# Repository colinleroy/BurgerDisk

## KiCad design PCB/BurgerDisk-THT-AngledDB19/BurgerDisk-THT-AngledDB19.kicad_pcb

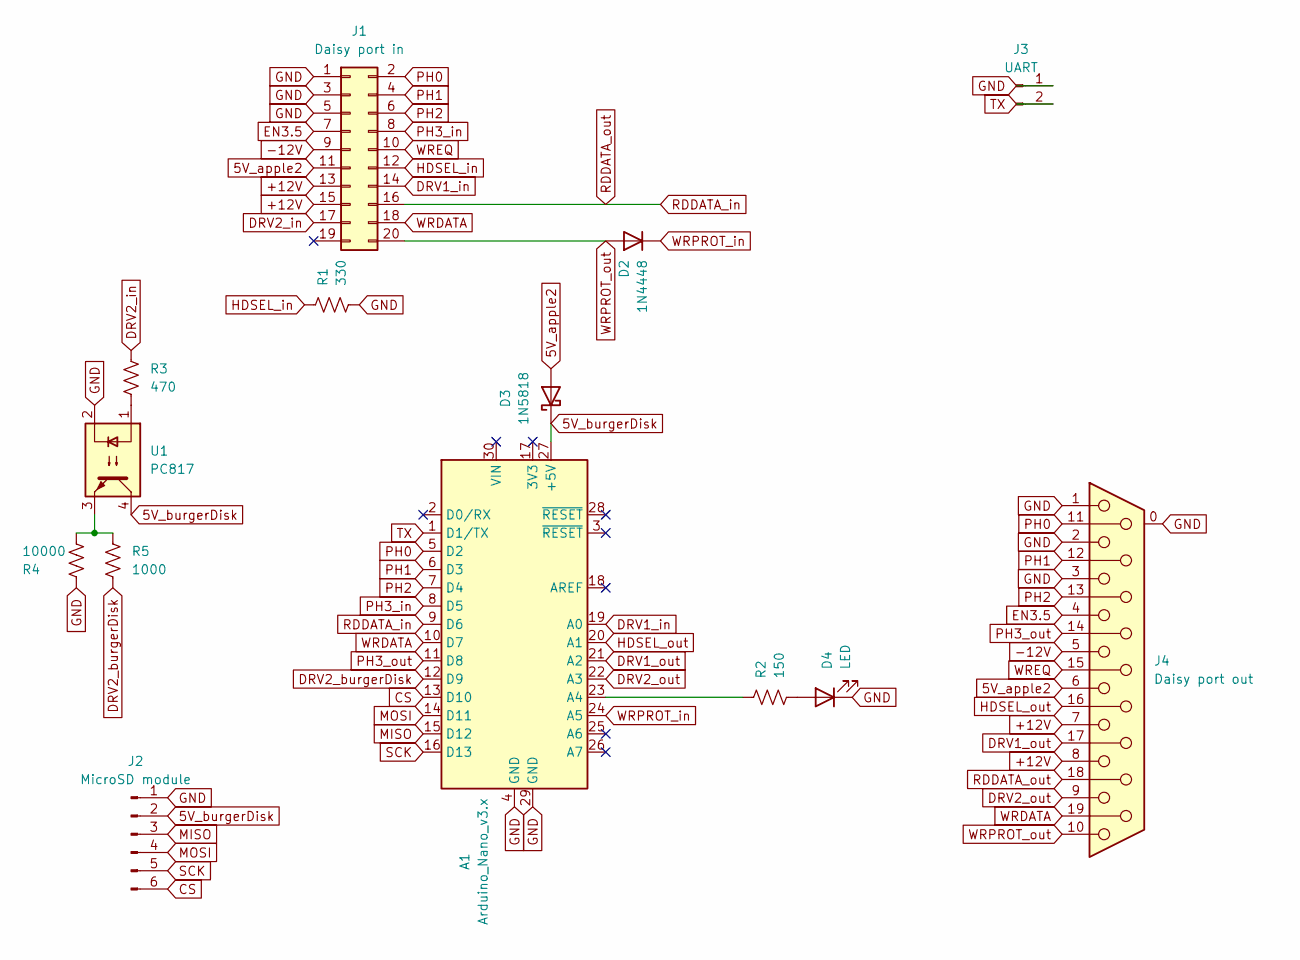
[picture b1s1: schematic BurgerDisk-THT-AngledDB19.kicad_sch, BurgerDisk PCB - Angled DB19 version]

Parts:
A1: Arduino_Nano_v3.x; Arduino_Nano
D2: 1N4448; D_DO-35_SOD27_P7.62mm_Horizontal; LCSC C258170
D3: 1N5818; D_DO-41_SOD81_P7.62mm_Horizontal; LCSC C402217
D4: LED; PinHeader_1x02_P2.54mm_Vertical; LCSC C6273326
J1: Daisy port in; IDC-Header_2x10_P2.54mm_Vertical; LCSC C3405
J2: MicroSD module; PinHeader_1x06_P2.54mm_Vertical; LCSC C56816
J3: UART; PinHeader_1x02_P2.54mm_Vertical; LCSC C6273326
J4: Daisy port out; DSUB-19_Female_Horizontal_MXS82009-8251-9246
R1: 330; R_Axial_DIN0207_L6.3mm_D2.5mm_P7.62mm_Horizontal; LCSC C58608
R2: 150; R_Axial_DIN0207_L6.3mm_D2.5mm_P7.62mm_Horizontal; LCSC C58668
R3: 470; R_Axial_DIN0309_L9.0mm_D3.2mm_P12.70mm_Horizontal; LCSC C129899
R4: 10000; R_Axial_DIN0207_L6.3mm_D2.5mm_P7.62mm_Horizontal; LCSC C57436
R5: 1000; R_Axial_DIN0207_L6.3mm_D2.5mm_P7.62mm_Horizontal; LCSC C57435
U1: PC817; DIP-4_W7.62mm; LCSC C5350

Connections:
5V_apple2: D3.2 (A), J1.11, J4.6
5V_burgerDisk: A1.27 (+5V), D3.1 (K), J2.2, U1.4
+12V: J1.13, J1.15, J4.7, J4.8
-12V: J1.9, J4.5
CS: A1.13 (D10), J2.6
DRV1_in: A1.19 (A0), J1.14
DRV1_out: A1.21 (A2), J4.17
DRV2_burgerDisk: A1.12 (D9), R5.1
DRV2_in: J1.17, R3.1
DRV2_out: A1.22 (A3), J4.9
EN3.5: J1.7, J4.4
GND: A1.4 (GND), A1.29 (GND), D4.1 (K), J1.1, J1.3, J1.5, J2.1, J3.1, J4.0, J4.1, J4.2, J4.3, R1.1, R4.1, U1.2
HDSEL_in: J1.12, R1.2
HDSEL_out: A1.20 (A1), J4.16
MISO: A1.15 (D12), J2.3
MOSI: A1.14 (D11), J2.4
unnamed: A1.23 (A4), R2.2
unnamed: D4.2 (A), R2.1
unnamed: R3.2, U1.1
unnamed: R4.2, R5.2, U1.3
PH0: A1.5 (D2), J1.2, J4.11
PH1: A1.6 (D3), J1.4, J4.12
PH2: A1.7 (D4), J1.6, J4.13
PH3_in: A1.8 (D5), J1.8
PH3_out: A1.11 (D8), J4.14
RDDATA_in: A1.9 (D6), J1.16, J4.18
SCK: A1.16 (D13), J2.5
TX: A1.1 (D1/TX), J3.2
WRDATA: A1.10 (D7), J1.18, J4.19
WREQ: J1.10, J4.15
WRPROT_in: A1.24 (A5), D2.1 (K)
WRPROT_out: D2.2 (A), J1.20, J4.10

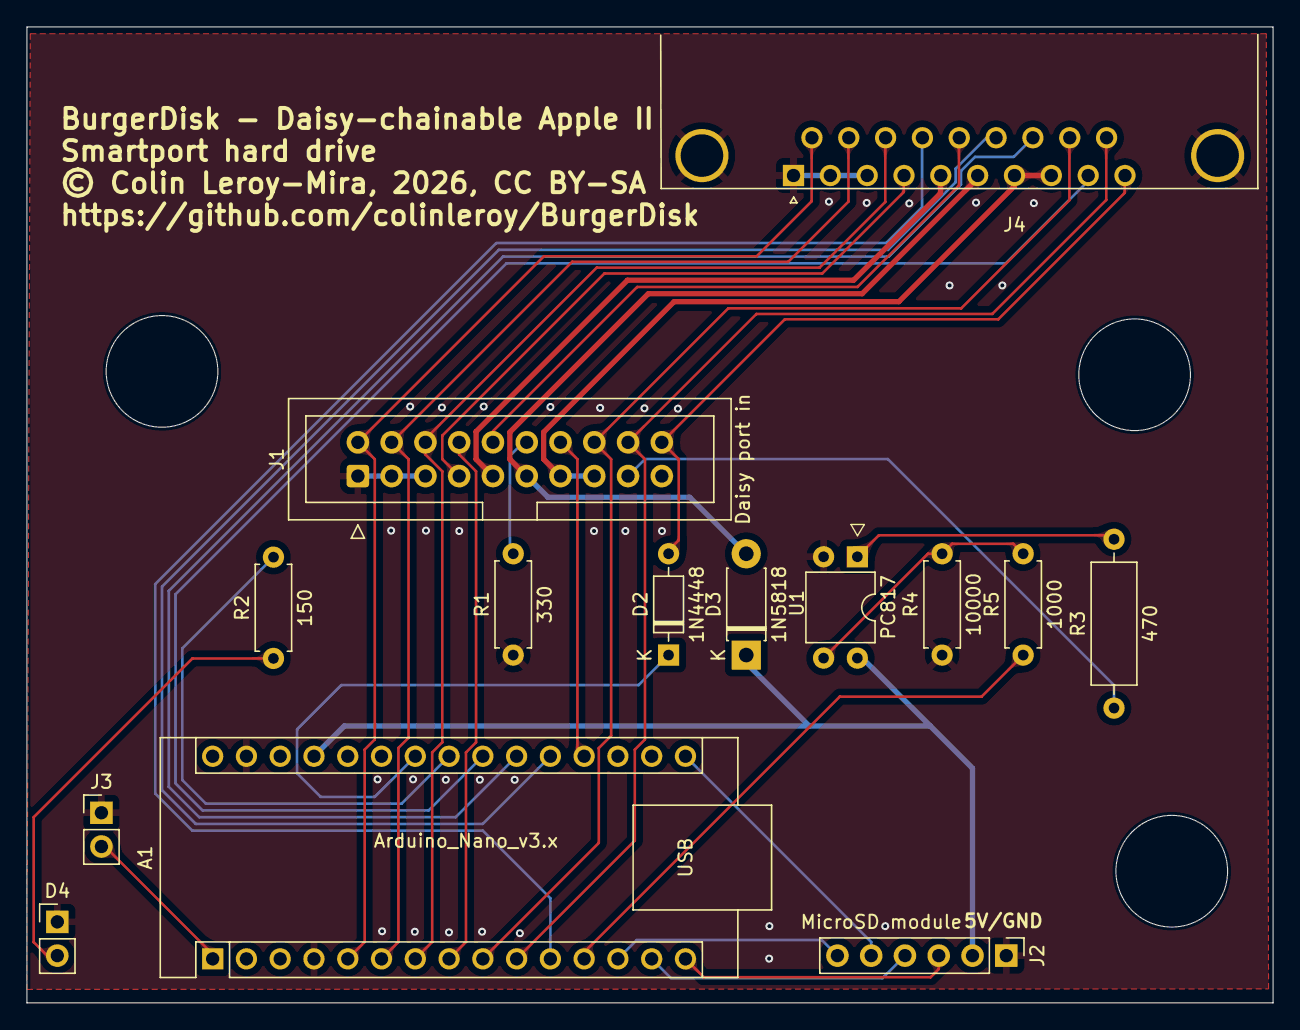
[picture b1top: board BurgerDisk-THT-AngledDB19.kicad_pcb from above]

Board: 2 copper layers, 93.7 x 73.4 mm, 14 parts (0 on the bottom side), 32 nets.

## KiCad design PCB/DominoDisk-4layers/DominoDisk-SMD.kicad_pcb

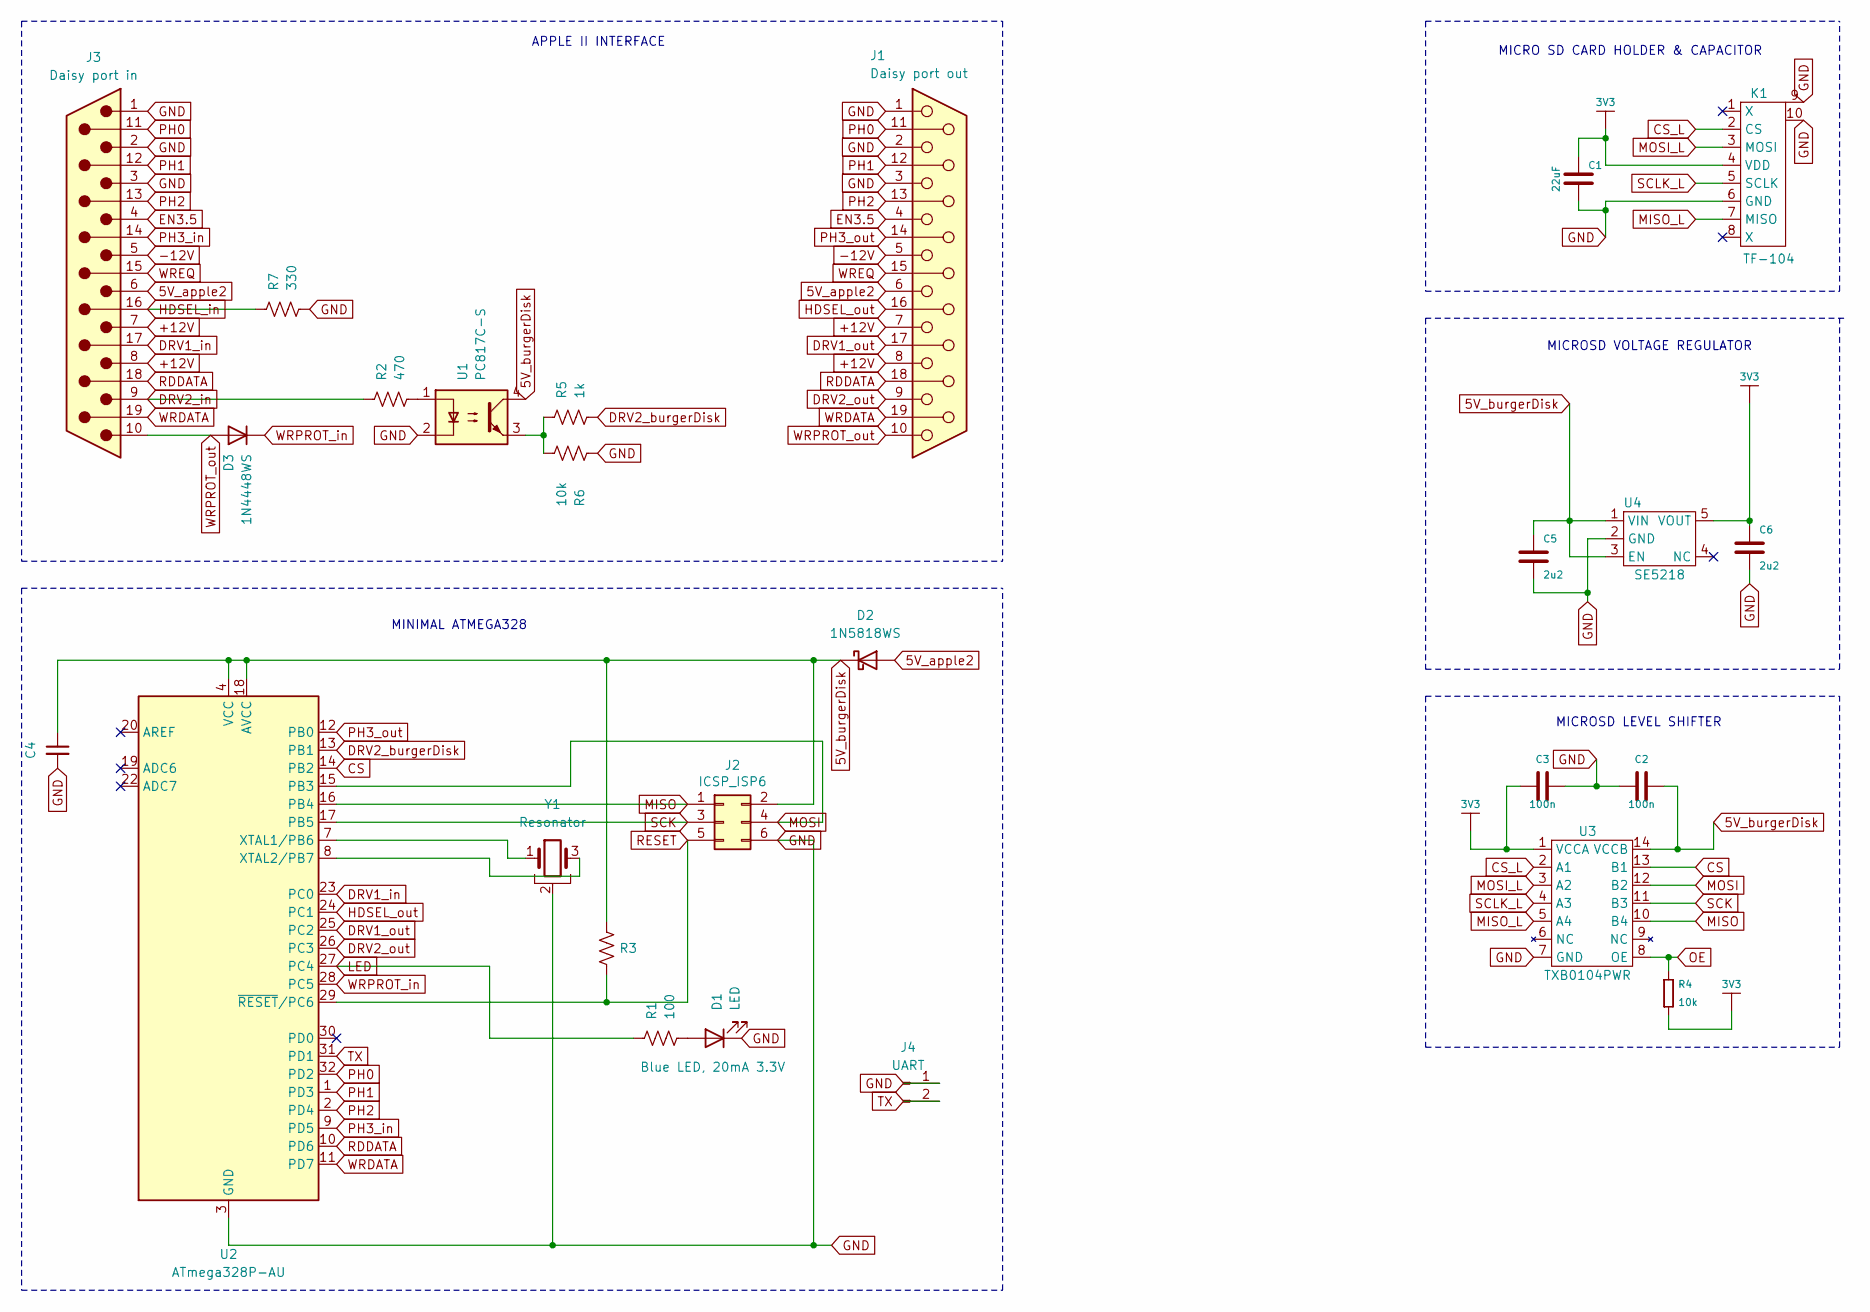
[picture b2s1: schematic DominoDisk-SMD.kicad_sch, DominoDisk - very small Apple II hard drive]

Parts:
C1: 22uF; C_0805_2012Metric; LCSC C45783
C2, C3, C4: 100n; C_0603_1608Metric; LCSC C1590
C5, C6: 2u2; C_0603_1608Metric; LCSC C1607
D1: LED; LED_0603_1608Metric; LCSC C965807
D2: 1N5818WS; D_SOD-123F; LCSC C51315007
D3: 1N4448WS; D_SOD-323F; LCSC C167101
J1: Daisy port out; DSUB-19_Female_EdgeMount_Pitch2.77mm
J2: ICSP_ISP6; PinHeader_2x03_P2.54mm_Horizontal; LCSC C492431
J3: Daisy port in; DSUB-19_Male_EdgeMount_Pitch2.77mm
J4: UART; PinHeader_1x02_P2.54mm_Vertical; LCSC-disabled C6273326 (disabled to avoid having to r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
K1: TF-104; TF-SMD_TF-104; LCSC C266612
R1: 100; R_0603_1608Metric; LCSC C22369795
R2: 470; R_1206_3216Metric; LCSC C137212
R3, R4, R6: 10k; R_0603_1608Metric; LCSC C177337
R5: 1k; R_0603_1608Metric; LCSC C177343
R7: 330; R_0603_1608Metric; LCSC C177341
U1: PC817C-S; SOP-4_3.8x4.1mm_P2.54mm; LCSC C3008369
U2: ATmega328P-AU; TQFP-32_7x7mm_P0.8mm; LCSC C14877
U3: TXB0104PWR; TSSOP-14-1EP_4.4x5mm_P0.65mm; LCSC C60708
U4: SE5218; SOT-23-5; LCSC C118233
Y1: Resonator; Resonator_SMD_Murata_CSTxExxV-3Pin_3.0x1.1mm; LCSC C341521

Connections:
3V3: C1.2, C3.1, C6.2, K1.4 (VDD), R4.1, U3.1 (VCCA), U4.5 (VOUT)
5V_apple2: D2.2 (A), J1.6, J3.6
5V_burgerDisk: C2.2, C4.1, C5.2, D2.1 (K), J2.2, R3.1, U1.4, U2.4 (VCC), U2.6 (VCC), U2.18 (AVCC), U3.14 (VCCB), U4.1 (VIN), U4.3 (EN)
+12V: J1.7, J1.8, J3.7, J3.8
-12V: J1.5, J3.5
CS: U2.14 (PB2), U3.13 (B1)
CS_L: K1.2 (CS), U3.2 (A1)
DRV1_in: J3.17, U2.23 (PC0)
DRV1_out: J1.17, U2.25 (PC2)
DRV2_burgerDisk: R5.1, U2.13 (PB1)
DRV2_in: J3.9, R2.1
DRV2_out: J1.9, U2.26 (PC3)
EN3.5: J1.4, J3.4
GND: C1.1, C2.1, C3.2, C4.2, C5.1, C6.1, D1.1 (K), J1.1, J1.2, J1.3, J2.6, J3.1, J3.2, J3.3, J4.1, K1.6 (GND), K1.9, K1.10, R6.1, R7.1, U1.2, U2.3 (GND), U2.5 (GND), U2.21 (GND), U3.7 (GND), U4.2 (GND), Y1.2
HDSEL_in: J3.16, R7.2
HDSEL_out: J1.16, U2.24 (PC1)
LED: R1.2, U2.27 (PC4)
MISO: J2.1, U2.16 (PB4), U3.10 (B4)
MISO_L: K1.7 (MISO), U3.5 (A4)
MOSI: J2.4, U2.15 (PB3), U3.12 (B2)
MOSI_L: K1.3 (MOSI), U3.3 (A2)
unnamed: D1.2 (A), R1.1
unnamed: R2.2, U1.1
unnamed: R5.2, R6.2, U1.3
unnamed: U2.7 (XTAL1/PB6), Y1.1
unnamed: U2.8 (XTAL2/PB7), Y1.3
OE: R4.2, U3.8 (OE)
PH0: J1.11, J3.11, U2.32 (PD2)
PH1: J1.12, J3.12, U2.1 (PD3)
PH2: J1.13, J3.13, U2.2 (PD4)
PH3_in: J3.14, U2.9 (PD5)
PH3_out: J1.14, U2.12 (PB0)
RDDATA: J1.18, J3.18, U2.10 (PD6)
RESET: J2.5, R3.2, U2.29 (~RESET/PC6)
SCK: J2.3, U2.17 (PB5), U3.11 (B3)
SCLK_L: K1.5 (SCLK), U3.4 (A3)
TX: J4.2, U2.31 (PD1)
WRDATA: J1.19, J3.19, U2.11 (PD7)
WREQ: J1.15, J3.15
WRPROT_in: D3.1 (K), U2.28 (PC5)
WRPROT_out: D3.2 (A), J1.10, J3.10

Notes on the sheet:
MICROSD LEVEL SHIFTER
MINIMAL ATMEGA328
MICROSD VOLTAGE REGULATOR
APPLE II INTERFACE
MICRO SD CARD HOLDER & CAPACITOR

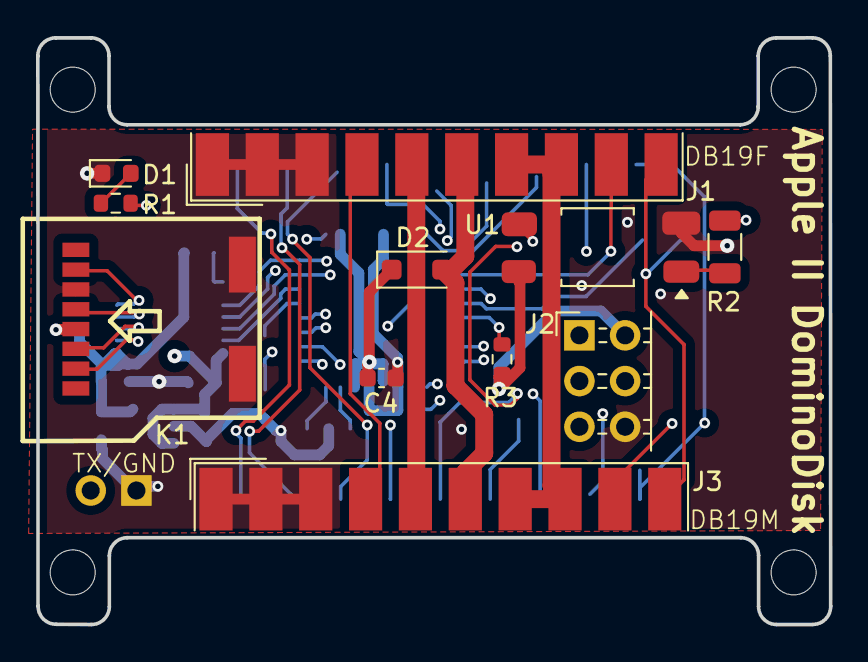
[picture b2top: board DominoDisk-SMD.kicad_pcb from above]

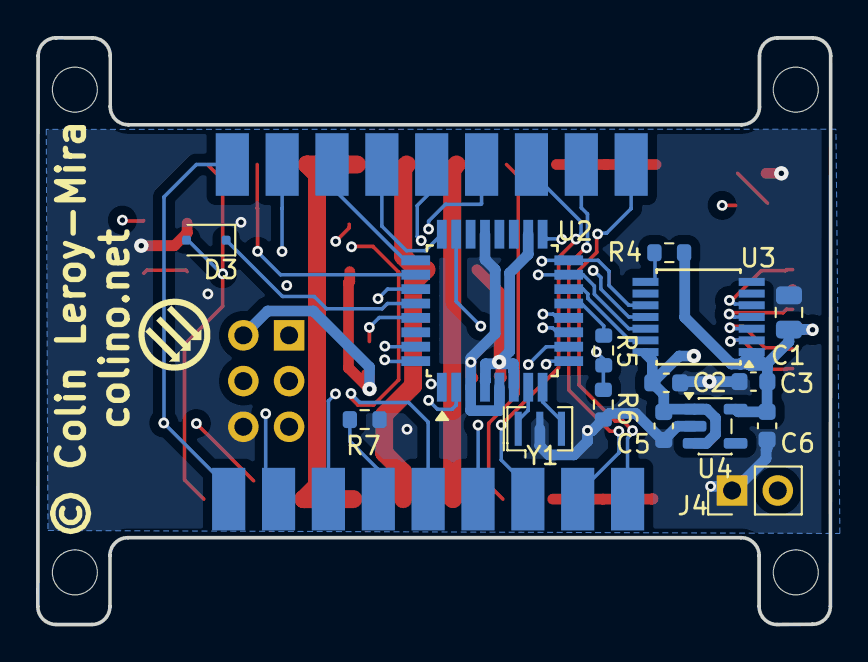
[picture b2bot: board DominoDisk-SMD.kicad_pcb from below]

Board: 4 copper layers, 44.0 x 32.6 mm, 26 parts (15 on the bottom side), 41 nets.

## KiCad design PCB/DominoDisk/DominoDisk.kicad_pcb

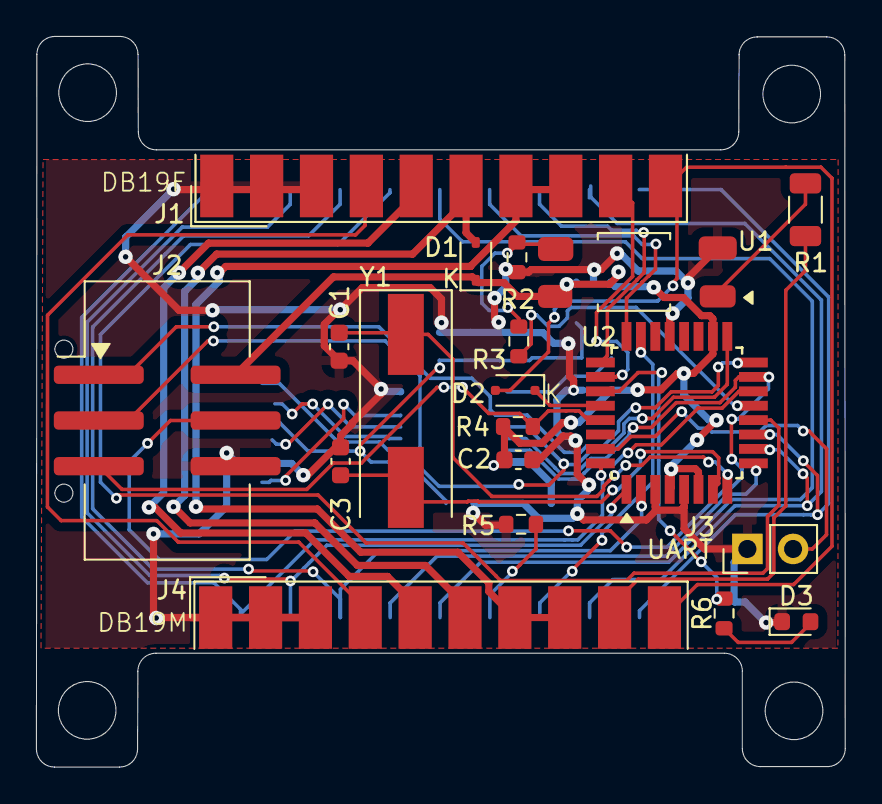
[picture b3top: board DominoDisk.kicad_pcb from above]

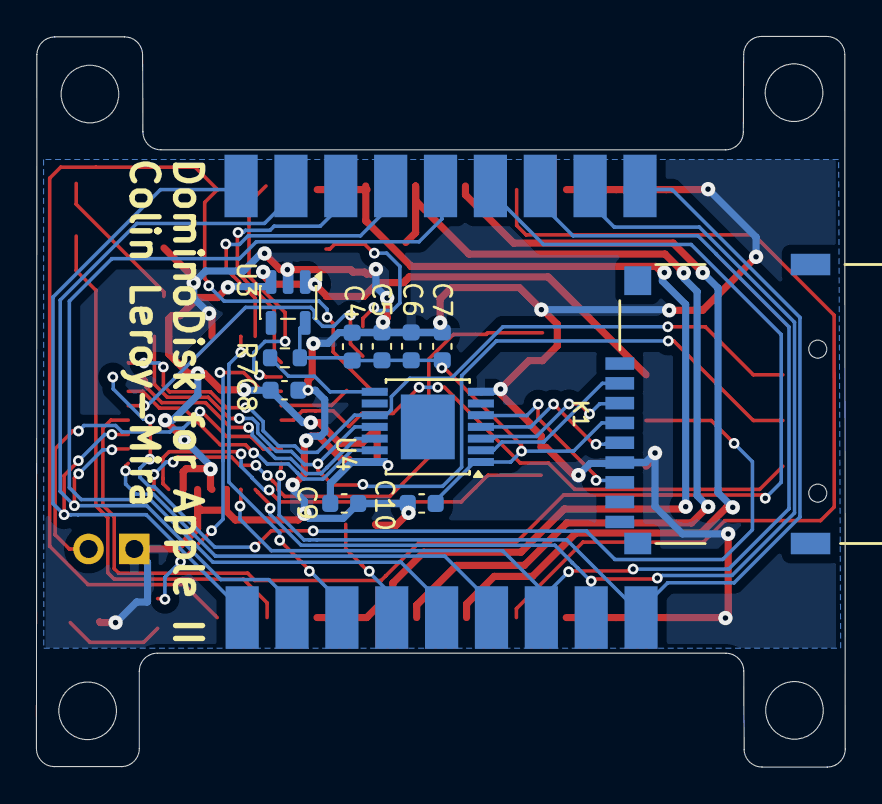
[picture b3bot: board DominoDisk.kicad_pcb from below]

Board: 2 copper layers, 44.9 x 40.6 mm, 30 parts (11 on the bottom side), 41 nets.

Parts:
C1, C3: 22pF; C_0603_1608Metric
C2: 100nF; C_0603_1608Metric
C4, C5, C8: 2u2; C_0603_1608Metric
C6, C7, C9, C10: 100n; C_0603_1608Metric
D1: 1N5818WS; D_SOD-323
D2: 1N4448WS; D_SOD-323F
D3: LED; LED_0603_1608Metric
J1: Daisy port out; DSUB-19_Female_EdgeMount_Pitch2.77mm
J2: ICSP_ISP6; IDC-Header_2x03_P2.54mm_Vertical_SMD
J3: UART; PinHeader_1x02_P2.54mm_Vertical
J4: Daisy port in; DSUB-19_Male_EdgeMount_Pitch2.77mm
K1: HYC77-TF09-200; MICROSD-HYC77-TF09-200
R1: 470; R_1206_3216Metric
R2, R7: 10k; R_0603_1608Metric
R3: 1k; R_0603_1608Metric
R4: 10K; R_0603_1608Metric
R5: 330; R_0603_1608Metric
R6: 150; R_0603_1608Metric
U1: PC817C-S; SOP-4_3.8x4.1mm_P2.54mm
U2: ATmega328P-AU; TQFP-32_7x7mm_P0.8mm
U3: SE5218; SOT-23-5
U4: TXB0104QPWRQ1; TSSOP-14-1EP_4.4x5mm_P0.65mm
Y1: 16MHz; Crystal_SMD_HC49-SD

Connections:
3V3: C4.2, C5.2, C6.2, C7.2, C10.1, K1.4 (VDD), R7.1, U3.5 (VOUT), U4.1 (VCCA)
5V_apple2: D1.2 (A), J1.6, J4.6
5V_burgerDisk: C2.1, C8.2, C9.2, D1.1 (K), J2.2, R4.1, U1.4, U2.4 (VCC), U2.6 (VCC), U2.18 (AVCC), U3.1 (VIN), U3.3 (EN), U4.14 (VCCB)
+12V: J1.7, J1.8, J4.7, J4.8
-12V: J1.5, J4.5
CS: U2.14 (PB2), U4.13 (B1)
CS_L: K1.2 (CS), U4.2 (A1)
DRV1_in: J4.17, U2.23 (PC0)
DRV1_out: J1.17, U2.25 (PC2)
DRV2_burgerDisk: R3.1, U2.13 (PB1)
DRV2_in: J4.9, R1.1
DRV2_out: J1.9, U2.26 (PC3)
EN3.5: J1.4, J4.4
GND: C1.2, C2.2, C3.2, C4.1, C5.1, C6.1, C7.1, C8.1, C9.1, C10.2, D3.1 (K), J1.1, J1.2, J1.3, J2.6, J3.1, J4.1, J4.2, J4.3, K1.6 (GND), R2.1, R5.1, U1.2, U2.3 (GND), U2.5 (GND), U2.21 (GND), U3.2 (GND), U4.7 (GND)
HDSEL_in: J4.16, R5.2
HDSEL_out: J1.16, U2.24 (PC1)
LED: R6.2, U2.27 (PC4)
MISO: J2.1, U2.16 (PB4), U4.10 (B4)
MISO_L: K1.7 (MISO), U4.5 (A4)
MOSI: J2.4, U2.15 (PB3), U4.12 (B2)
MOSI_L: K1.3 (MOSI), U4.3 (A2)
unnamed: D3.2 (A), R6.1
unnamed: R1.2, U1.1
unnamed: R2.2, R3.2, U1.3
unnamed: C3.1, U2.7 (XTAL1/PB6), Y1.2
unnamed: C1.1, U2.8 (XTAL2/PB7), Y1.1
OE: R7.2, U4.8 (OE)
PH0: J1.11, J4.11, U2.32 (PD2)
PH1: J1.12, J4.12, U2.1 (PD3)
PH2: J1.13, J4.13, U2.2 (PD4)
PH3_in: J4.14, U2.9 (PD5)
PH3_out: J1.14, U2.12 (PB0)
RDDATA: J1.18, J4.18, U2.10 (PD6)
RESET: J2.5, R4.2, U2.29 (~RESET/PC6)
SCK: J2.3, U2.17 (PB5), U4.11 (B3)
SCLK_L: K1.5 (SCLK), U4.4 (A3)
TX: J3.2, U2.31 (PD1)
WRDATA: J1.19, J4.19, U2.11 (PD7)
WREQ: J1.15, J4.15
WRPROT_in: D2.1 (K), U2.28 (PC5)
WRPROT_out: D2.2 (A), J1.10, J4.10

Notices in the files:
PCB/BurgerDisk-THT-Angled/BurgerDisk-THT-AngledDB19.kicad_sch:
License: CC BY-SA
PCB/BurgerDisk-THT-AngledDB19/BurgerDisk-THT-AngledDB19.kicad_pcb:
© Colin Leroy-Mira, 2026, CC BY-SA
